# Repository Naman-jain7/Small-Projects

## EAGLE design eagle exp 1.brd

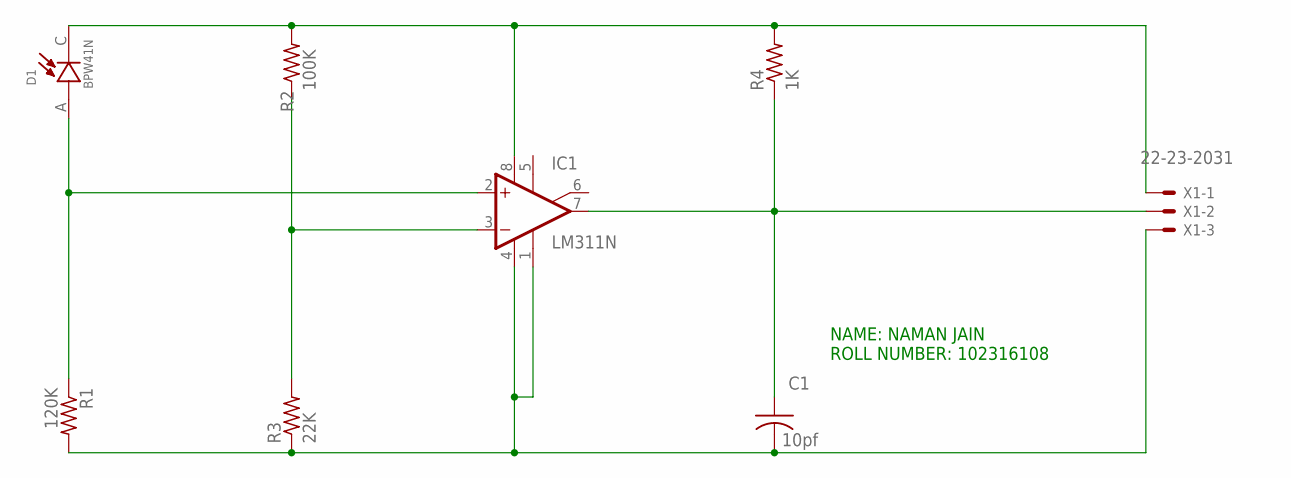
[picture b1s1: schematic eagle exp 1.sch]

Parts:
C1: 10pf; C025-024X044
D1: BPW41N; DIO_BPW41N
IC1: LM311N; DIL08
R1: 120K; 0204/5
R2: 100K; 0204/5
R3: 22K; 0204/5
R4: 1K; 0204/5
X1: 22-23-2031

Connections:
unnamed: D1.C, IC1.8 (V+), R2.2, R4.2, X1.1
unnamed: D1.A, IC1.2 (+IN), R1.1
unnamed: C1.2, IC1.1 (GND), IC1.4 (V-), R1.2, R3.1, X1.3
unnamed: IC1.3 (-IN), R2.1, R3.2
unnamed: C1.1, IC1.7 (OUT), R4.1, X1.2

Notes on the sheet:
NAME: NAMAN JAIN ROLL NUMBER: 102316108

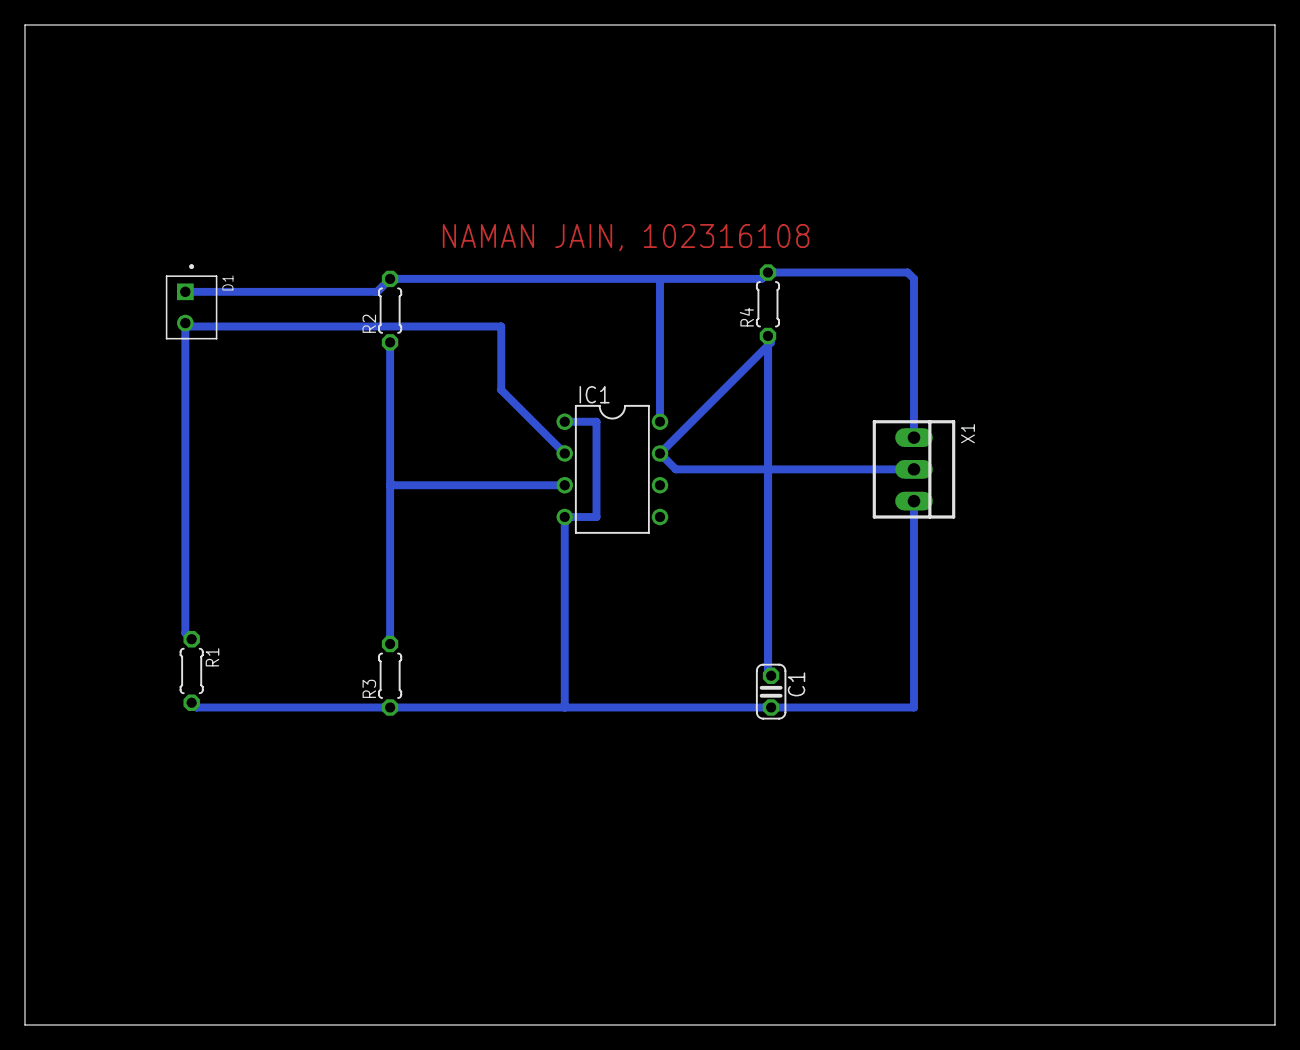
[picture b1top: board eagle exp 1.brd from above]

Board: 2 copper layers, 100.0 x 80.0 mm, 8 parts (0 on the bottom side), 5 nets.

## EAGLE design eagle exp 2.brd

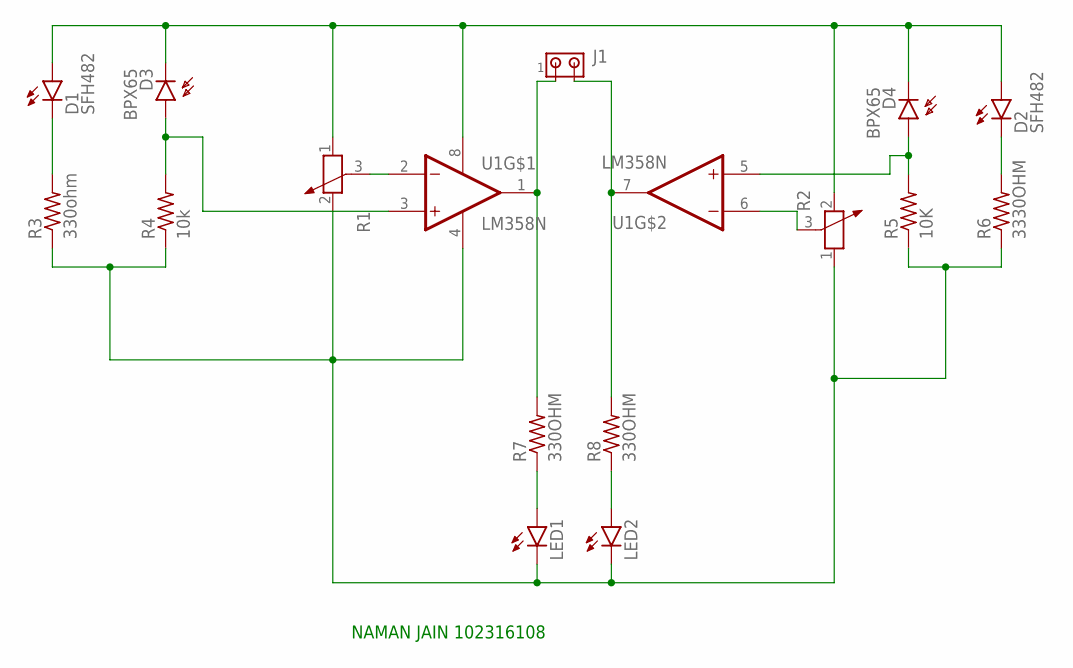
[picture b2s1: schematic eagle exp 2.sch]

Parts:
D1, D2: SFH482
D3, D4: BPX65
J1: MTA02-100; 10X02MTA
LED1, LED2: LED3MM
R1, R2: POTENTIOMETER_PT-10; PT-10
R3: 330ohm; 0204/5
R4: 10k; 0204/5
R5: 10K; 0204/5
R6: 3330OHM; 0204/5
R7, R8: 330OHM; 0204/5
U1: LM358N; DIP762W46P254L960H508Q8

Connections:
unnamed: R1.3, U1.2 (1IN-)
unnamed: D1.K (C), R3.2
unnamed: D2.K (C), R6.2
unnamed: D4.A, R5.2, U1.5 (2IN+)
unnamed: LED1.K (C), LED2.K (C), R1.2, R2.1, R3.1, R4.1, R5.1, R6.1, U1.4 (GND)
unnamed: R2.3, U1.6 (2IN-)
unnamed: D1.A, D2.A, D3.K (C), D4.K (C), R1.1, R2.2, U1.8 (VCC)
unnamed: J1.1, R7.2, U1.1 (1OUT)
unnamed: J1.2, R8.2, U1.7 (2OUT)
unnamed: LED1.A, R7.1
unnamed: LED2.A, R8.1
unnamed: D3.A, R4.2, U1.3 (1IN+)

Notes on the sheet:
NAMAN JAIN 102316108

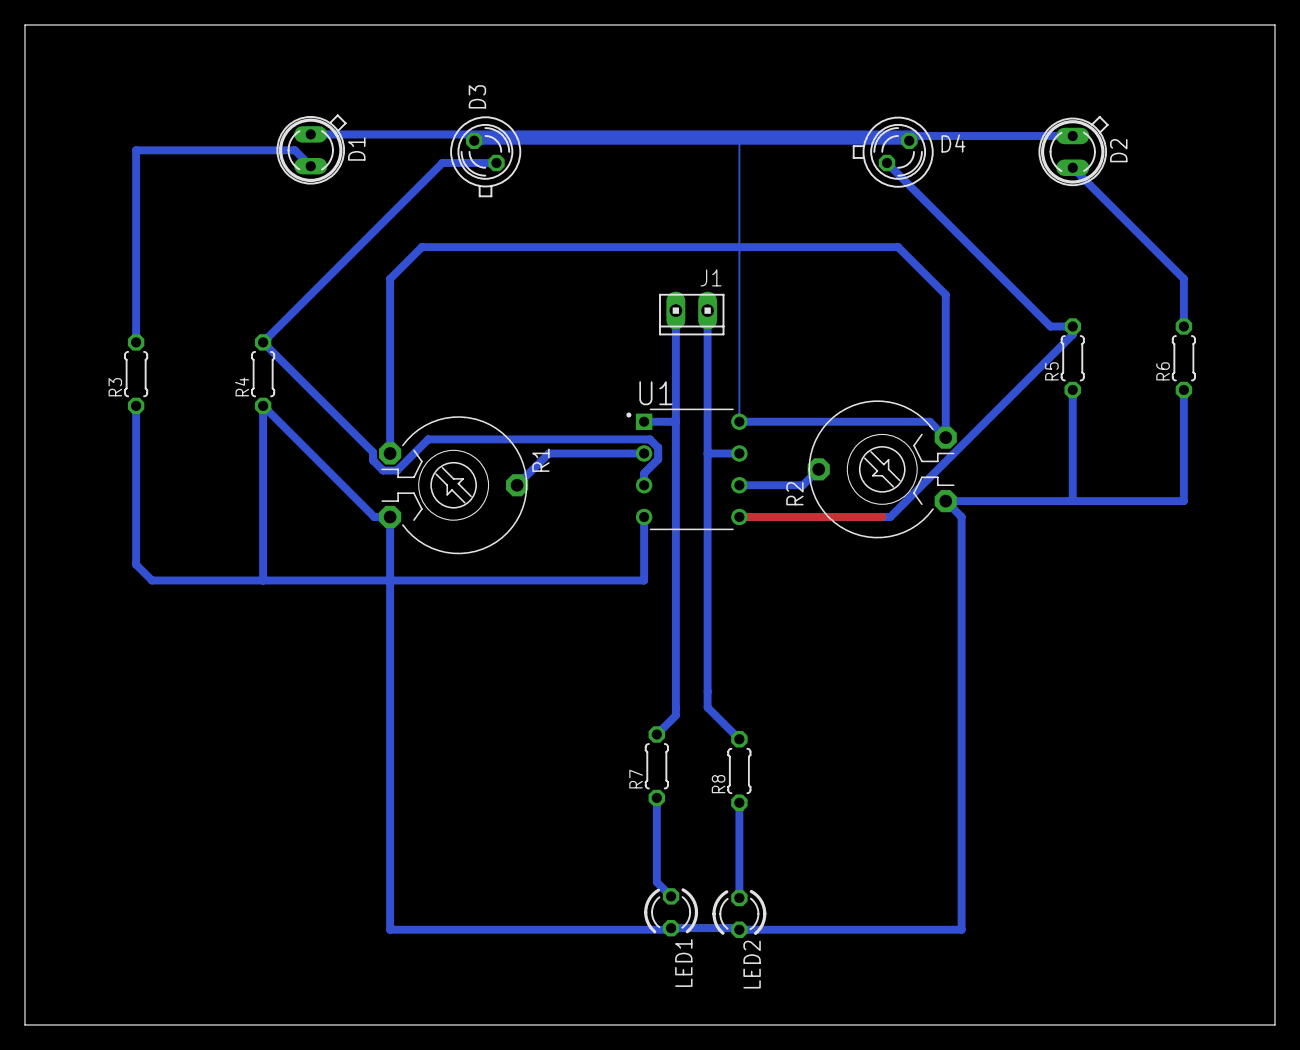
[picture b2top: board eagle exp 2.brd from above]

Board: 2 copper layers, 100.0 x 80.0 mm, 16 parts (0 on the bottom side), 12 nets.

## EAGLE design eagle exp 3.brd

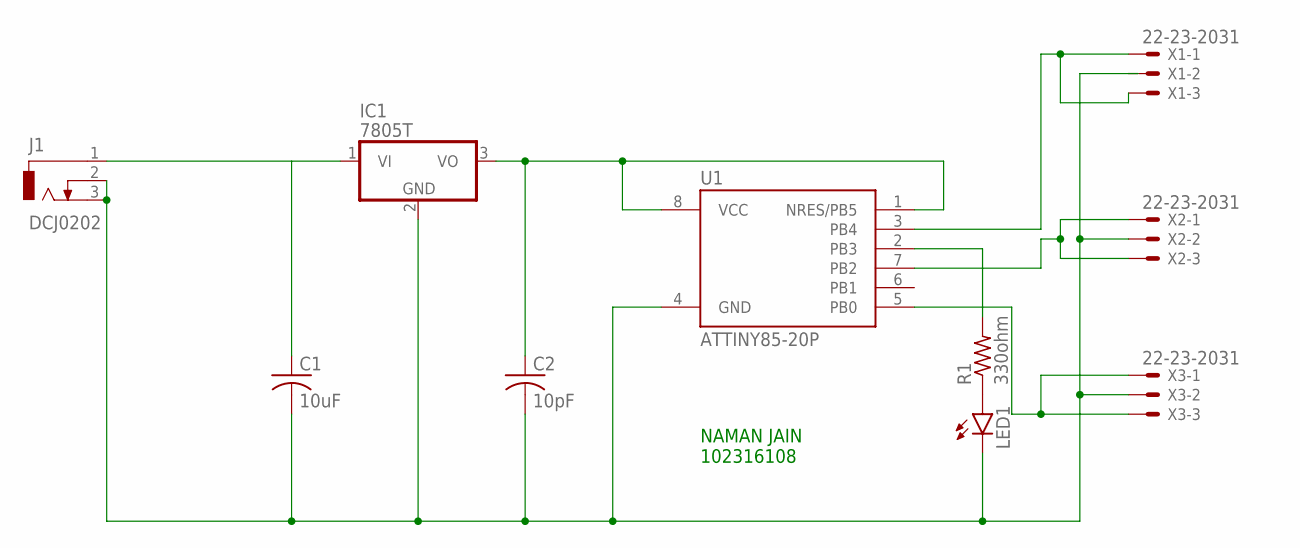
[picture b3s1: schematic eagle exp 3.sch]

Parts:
C1: 10uF; C025-024X044
C2: 10pF; C025-024X044
IC1: 7805T; TO220H
J1: DCJ0202
LED1: LED3MM
R1: 330ohm; 0207/5V
U1: ATTINY85-20P; PDIP08_300MIL
X1, X2, X3: 22-23-2031

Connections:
unnamed: LED1.A, R1.1
unnamed: IC1.1 (VI), J1.1
unnamed: C1.2, C2.2, IC1.2 (GND), J1.2, J1.3, LED1.K (C), U1.4 (GND), X1.2, X2.2, X3.2
unnamed: C2.1, IC1.3 (VO), U1.1 (NRES/PB5), U1.8 (VCC)
unnamed: U1.3 (PB4), X1.1, X1.3
unnamed: U1.7 (PB2), X2.1, X2.3
unnamed: R1.2, U1.2 (PB3)
unnamed: U1.5 (PB0), X3.1, X3.3

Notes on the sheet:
NAMAN JAIN 102316108

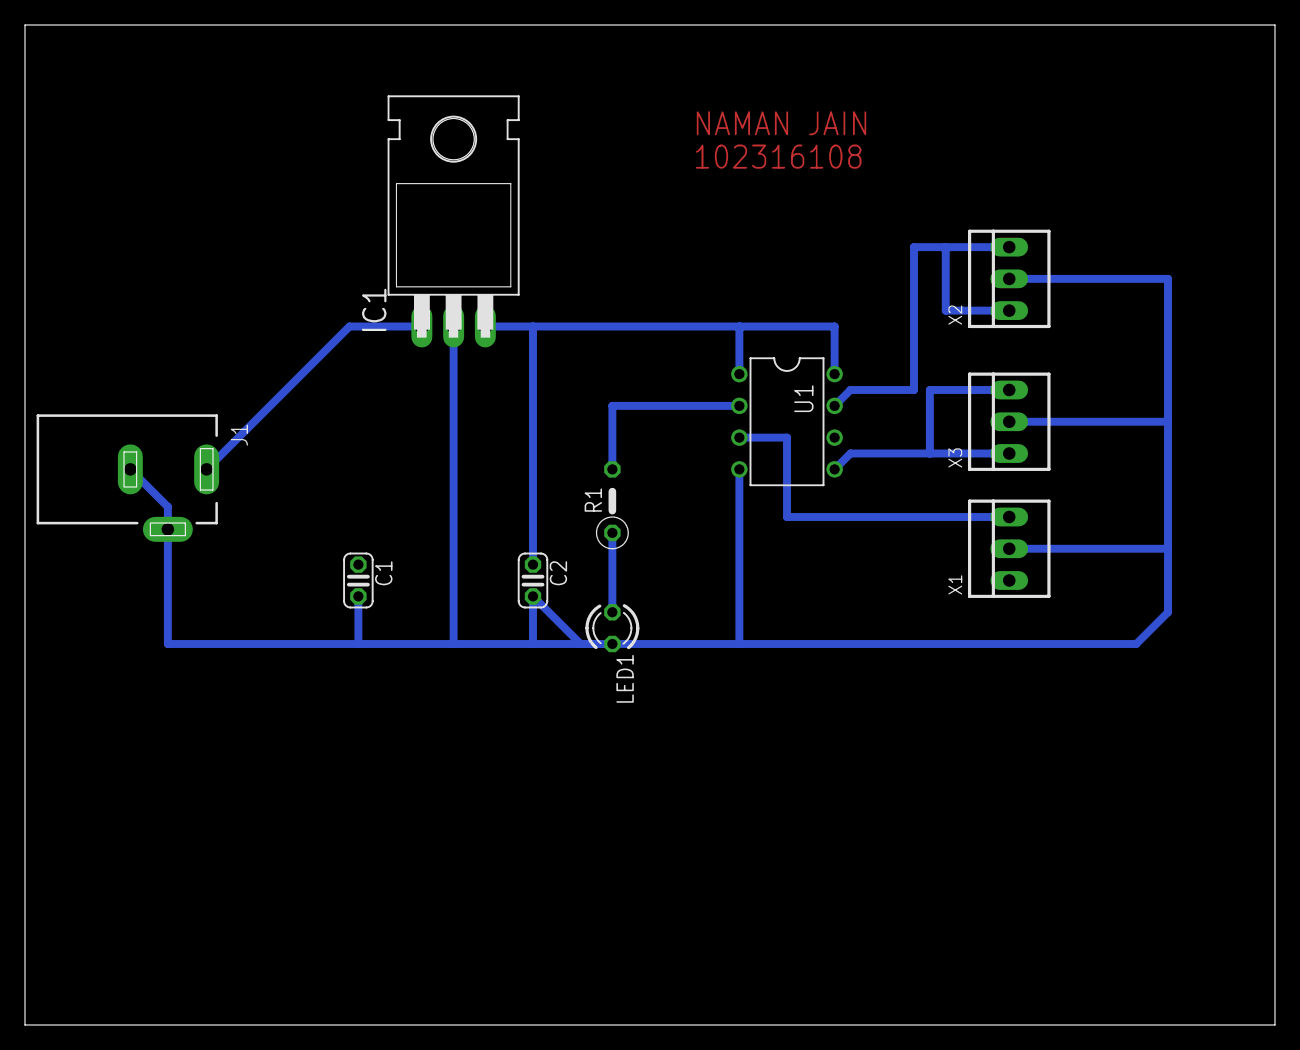
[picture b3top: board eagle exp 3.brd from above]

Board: 2 copper layers, 100.0 x 80.0 mm, 10 parts (0 on the bottom side), 8 nets.

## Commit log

2025-04-05 added face_recognition subfolder
2025-04-05 added files and val
2025-04-05 added face_recognition
2025-04-05 added files
2025-04-05 added folders
